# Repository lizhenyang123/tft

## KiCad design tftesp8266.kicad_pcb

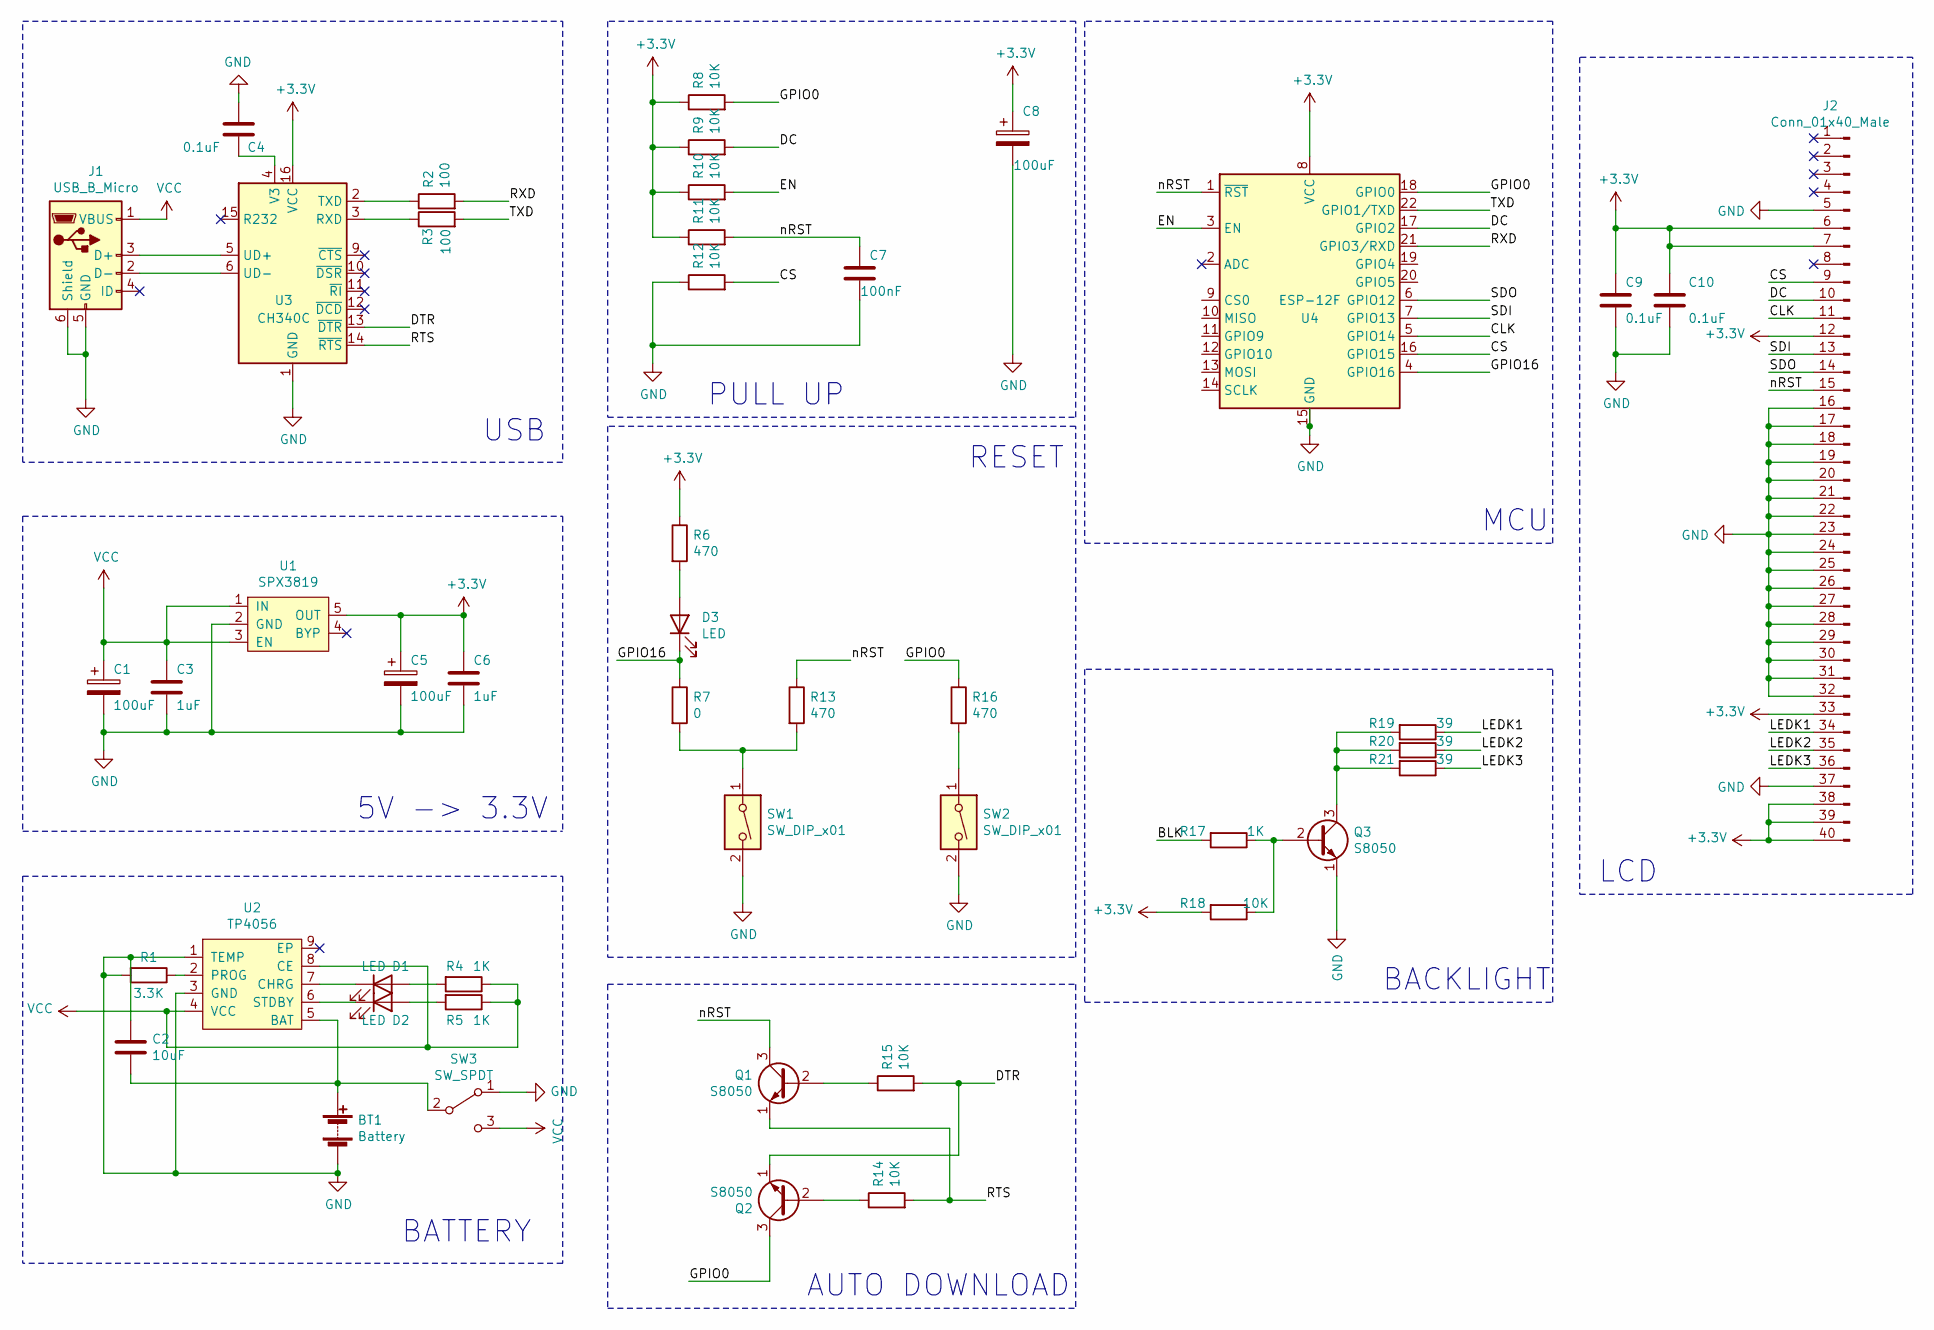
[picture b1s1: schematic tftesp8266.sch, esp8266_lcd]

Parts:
BT1: Battery; BATTRY
C1, C5, C8: 100uF; CP_EIA-3528-12_Kemet-T_Pad1.50x2.35mm_HandSolder
C2: 10uF; C_0603_1608Metric_Pad1.05x0.95mm_HandSolder
C3, C6: 1uF; C_0603_1608Metric_Pad1.05x0.95mm_HandSolder
C4, C9, C10: 0.1uF; C_0603_1608Metric_Pad1.05x0.95mm_HandSolder
C7: 100nF; C_0603_1608Metric_Pad1.05x0.95mm_HandSolder
D1, D2, D3: LED; LED_0603_1608Metric_Pad1.05x0.95mm_HandSolder
J1: USB_B_Micro; USB_Micro-B_Molex-105017-0001
J2: Conn_01x40_Male; Hirose_FH12-40S-0.5SH_1x40-1MP_P0.50mm_Horizontal
Q1, Q2, Q3: S8050; SOT-23
R1: 3.3K; R_0603_1608Metric_Pad1.05x0.95mm_HandSolder
R2, R3: 100; R_0603_1608Metric_Pad1.05x0.95mm_HandSolder
R4, R5, R17: 1K; R_0603_1608Metric_Pad1.05x0.95mm_HandSolder
R6, R13, R16: 470; R_0603_1608Metric_Pad1.05x0.95mm_HandSolder
R7: 0; R_0603_1608Metric_Pad1.05x0.95mm_HandSolder
R8, R9, R10, R11, R12, R14, R15, R18: 10K; R_0603_1608Metric_Pad1.05x0.95mm_HandSolder
R19, R20, R21: 39; R_0603_1608Metric_Pad1.05x0.95mm_HandSolder
SW1, SW2: SW_DIP_x01; SW_SPST_CK_RS282G05A3
SW3: SW_SPDT; SW_SPDT_PCM12
U1: SPX3819; SOT-23-5
U2: TP4056; HSOP-8-1EP_3.9x4.9mm_P1.27mm_EP2.41x3.1mm
U3: CH340C; SOIC-16_3.9x9.9mm_P1.27mm
U4: ESP-12F; ESP-12E

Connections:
+3V3: C5.1, C6.1, C8.1, C9.1, C10.1, J2.6, J2.7, J2.12, J2.33, J2.38, J2.39, J2.40, R6.1, R8.1, R9.1, R10.1, R11.1, R18.2, U1.5 (OUT~), U3.16 (VCC), U4.8 (VCC)
/CLK: J2.11, U4.5 (GPIO14)
/CS: J2.9, R12.2, U4.16 (GPIO15)
/DC: J2.10, R9.2, U4.17 (GPIO2)
/DTR: Q2.1 (E), R15.2, U3.13 (~DTR)
/EN: R10.2, U4.3 (EN)
/GPIO0: Q2.3 (C), R8.2, R16.1, U4.18 (GPIO0)
/GPIO16: D3.1 (K), R7.1, U4.4 (GPIO16)
/LEDK1: J2.34, R19.1
/LEDK2: J2.35, R20.1
/LEDK3: J2.36, R21.1
/RTS: Q1.1 (E), R14.2, U3.14 (~RTS)
/RXD: R2.2, U4.21 (GPIO3/RXD)
/SDI: J2.13, U4.7 (GPIO13)
/SDO: J2.14, U4.6 (GPIO12)
/TXD: R3.2, U4.22 (GPIO1/TXD)
/nRST: C7.1, J2.15, Q1.3 (C), R11.2, R13.1, U4.1 (~RST)
GND: BT1.2 (-), C1.2, C2.1, C3.2, C4.2, C5.2, C6.2, C7.2, C8.2, C9.2, C10.2, J1.5 (GND), J1.6 (Shield), J2.5, J2.16, J2.17, J2.18, J2.19, J2.20, J2.21, J2.22, J2.23, J2.24, J2.25, J2.26, J2.27, J2.28, J2.29, J2.30, J2.31, J2.32, J2.37, Q3.1 (E), R1.2, R12.1, SW1.2, SW2.2, SW3.1 (A), U1.2 (GND~), U2.1 (TEMP), U2.3 (GND), U3.1 (GND), U4.15 (GND)
unnamed: BT1.1 (+), C2.2, SW3.2 (B), U2.5 (BAT~)
unnamed: C4.1, U3.4 (V3)
unnamed: D1.1 (K), U2.7 (CHRG~)
unnamed: D1.2 (A), R4.2
unnamed: D2.1 (K), U2.6 (STDBY~)
unnamed: D2.2 (A), R5.2
unnamed: D3.2 (A), R6.2
unnamed: J1.2 (D-), U3.6 (UD-)
unnamed: J1.3 (D+), U3.5 (UD+)
unnamed: Q1.2 (B), R15.1
unnamed: Q2.2 (B), R14.1
unnamed: Q3.2 (B), R17.1, R18.1
unnamed: Q3.3 (C), R19.2, R20.2, R21.2
unnamed: R1.1, U2.2 (PROG)
unnamed: R2.1, U3.2 (TXD)
unnamed: R3.1, U3.3 (RXD)
unnamed: R7.2, R13.2, SW1.1
unnamed: R16.2, SW2.1
VCC: C1.1, C3.1, J1.1 (VBUS), R4.1, R5.1, SW3.3 (C), U1.1 (IN~), U1.3 (EN~), U2.4 (VCC), U2.8 (CE~)

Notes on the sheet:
5V -> 3.3V
BATTERY
AUTO DOWNLOAD
RESET
USB
MCU
BACKLIGHT
LCD
PULL UP

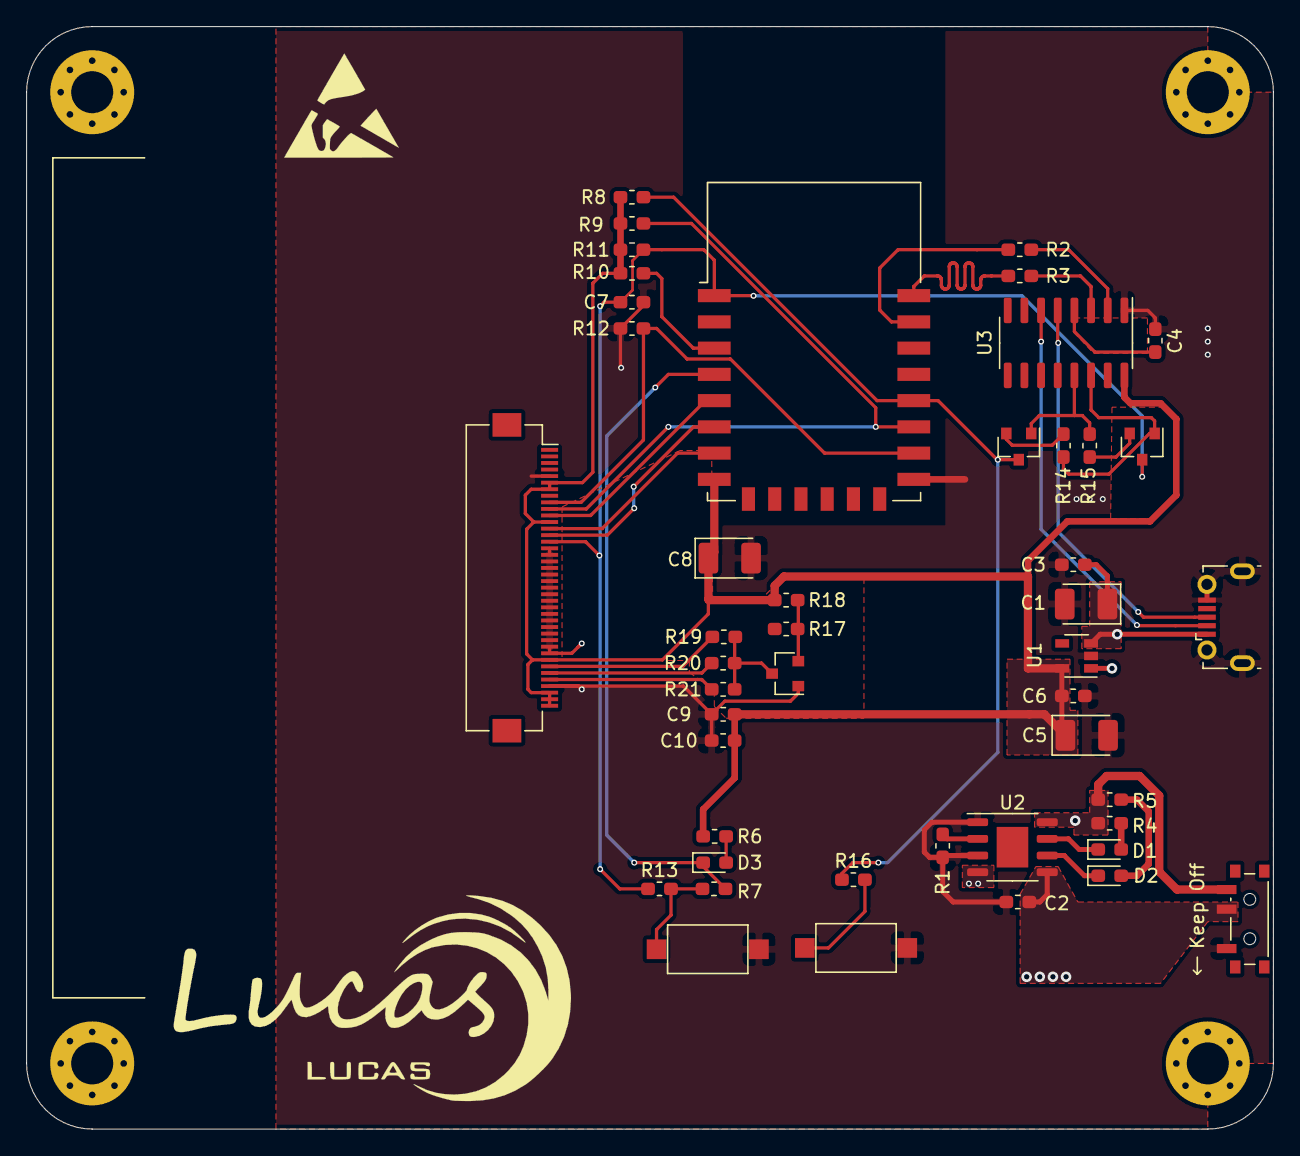
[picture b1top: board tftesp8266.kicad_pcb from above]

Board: 2 copper layers, 95.0 x 84.0 mm, 47 parts (1 on the bottom side), 37 nets.

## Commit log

2020-08-30 add file
2020-09-06 add bom
